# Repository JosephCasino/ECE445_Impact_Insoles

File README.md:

# ECE445_Impact_Insoles
ECE445 Group 68: Impact Insoles - Pressure Sensor System for Running Shoes
Created by: Joseph Casino, Aarush Sivanesan, Matthew Weng

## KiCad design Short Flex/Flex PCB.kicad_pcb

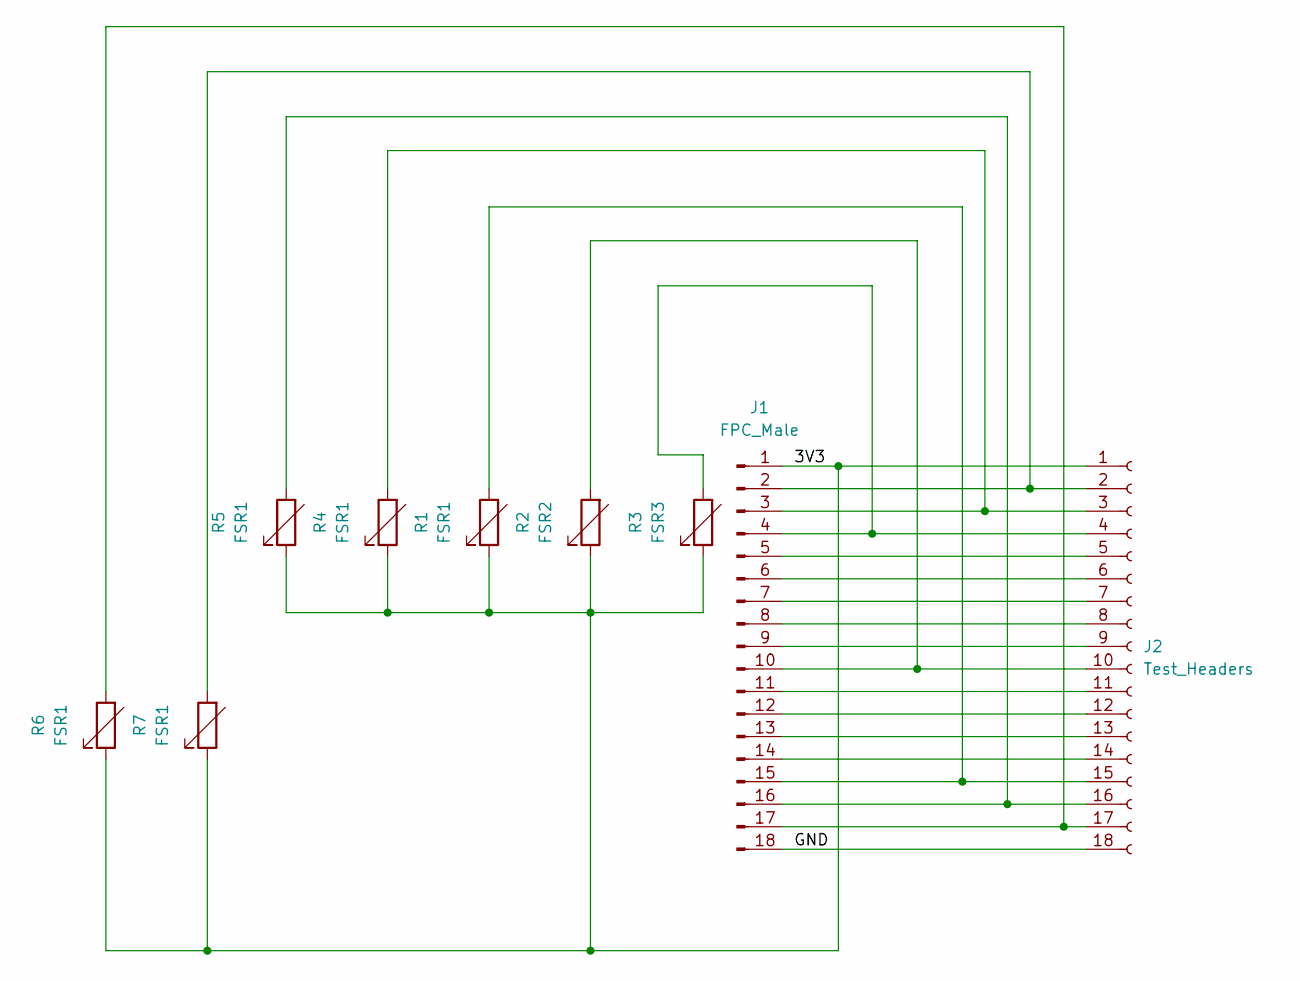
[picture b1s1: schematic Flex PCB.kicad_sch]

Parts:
J1: FPC_Male; FPC-Male-18P-1mm
J2: Test_Headers; PinSocket_1x18_P2.54mm_Vertical
R1, R4, R5, R6, R7: FSR1; FSR_402
R2: FSR2; FSR_402
R3: FSR3; FSR_402

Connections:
/3V3: J1.1, J2.1, R1.1, R2.1, R3.1, R4.1, R5.1, R6.1, R7.1
/GND: J1.18, J2.18
unnamed: J1.2, J2.2, R7.2
unnamed: J1.3, J2.3, R4.2
unnamed: J1.4, J2.4, R3.2
unnamed: J1.5, J2.5
unnamed: J1.6, J2.6
unnamed: J1.7, J2.7
unnamed: J1.8, J2.8
unnamed: J1.9, J2.9
unnamed: J1.10, J2.10, R2.2
unnamed: J1.11, J2.11
unnamed: J1.12, J2.12
unnamed: J1.13, J2.13
unnamed: J1.14, J2.14
unnamed: J1.15, J2.15, R1.2
unnamed: J1.16, J2.16, R5.2
unnamed: J1.17, J2.17, R6.2

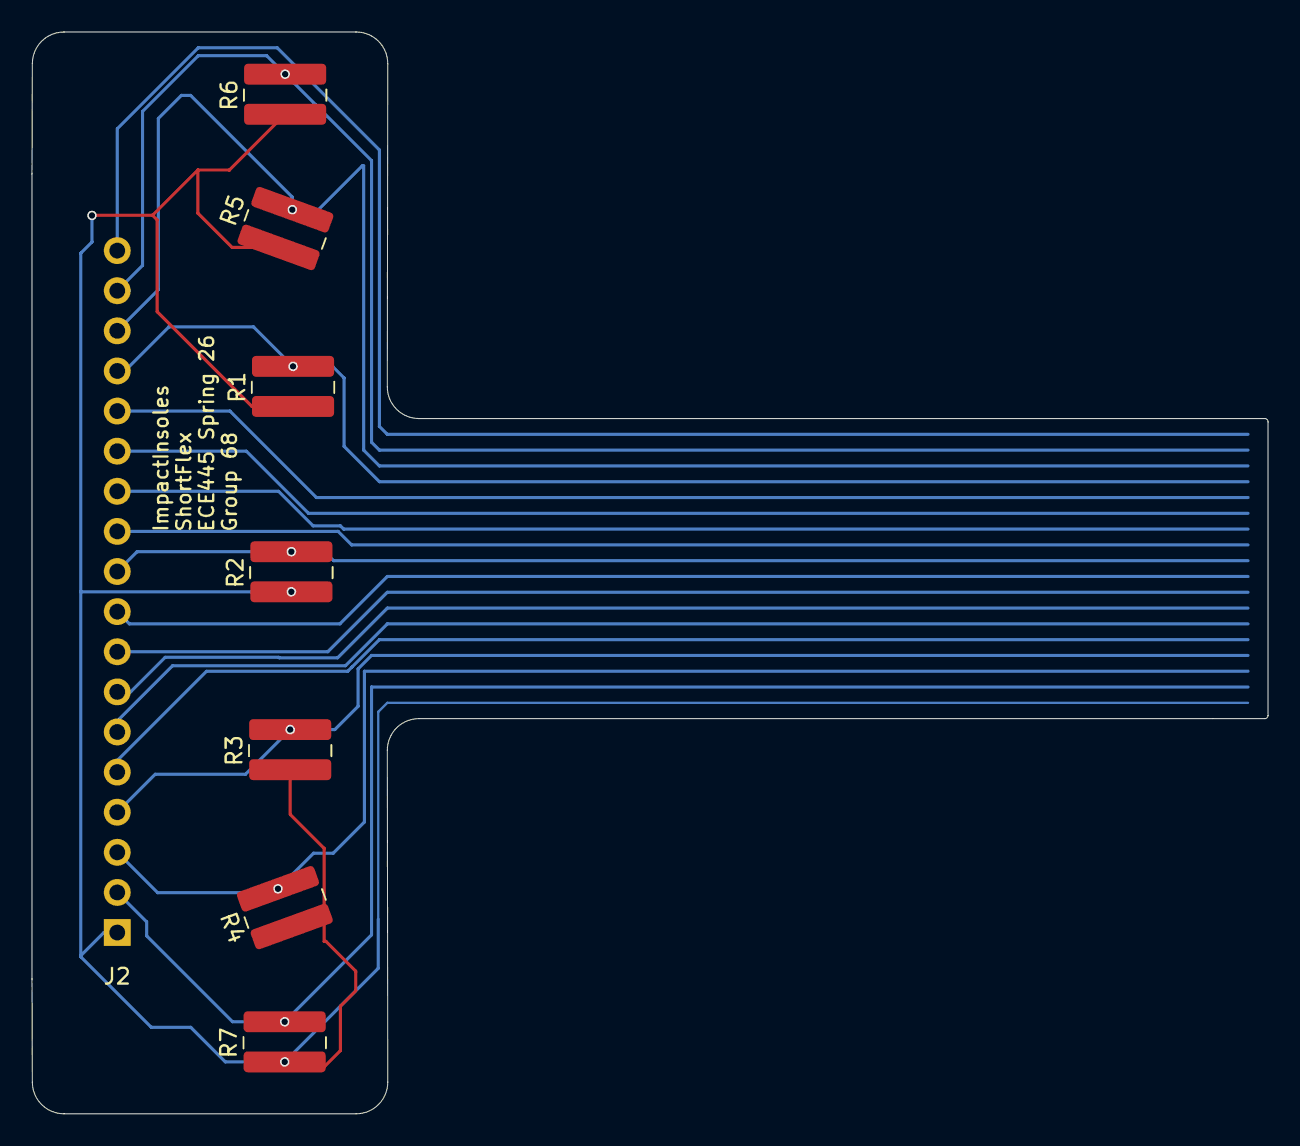
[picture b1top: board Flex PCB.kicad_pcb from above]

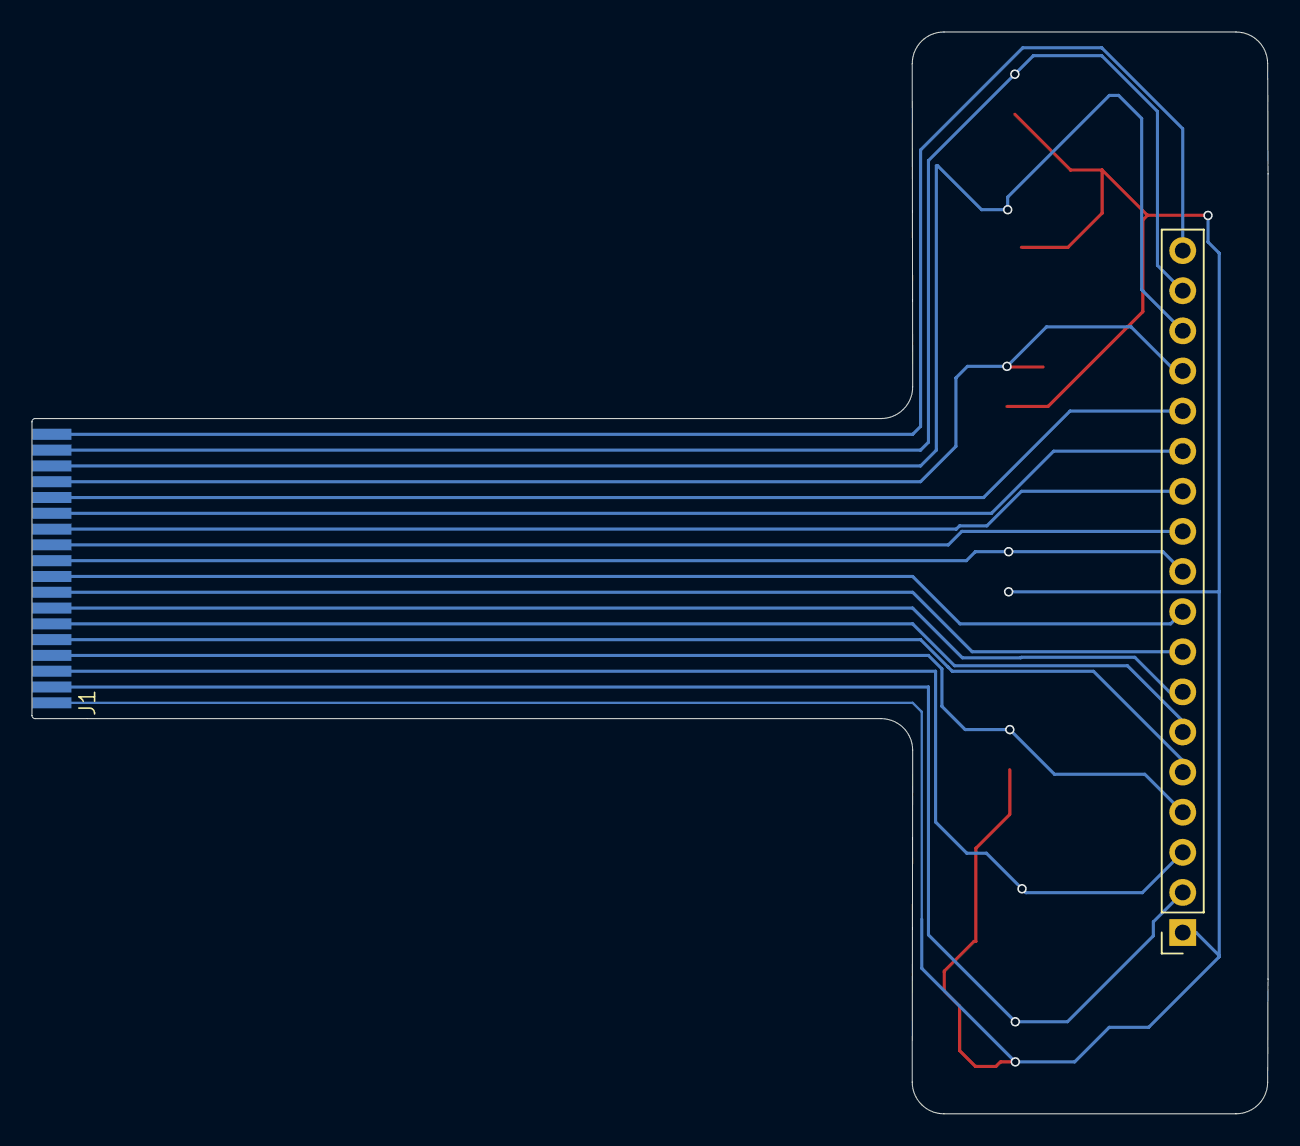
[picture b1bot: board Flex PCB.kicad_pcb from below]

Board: 2 copper layers, 78.3 x 68.5 mm, 9 parts (2 on the bottom side), 18 nets.

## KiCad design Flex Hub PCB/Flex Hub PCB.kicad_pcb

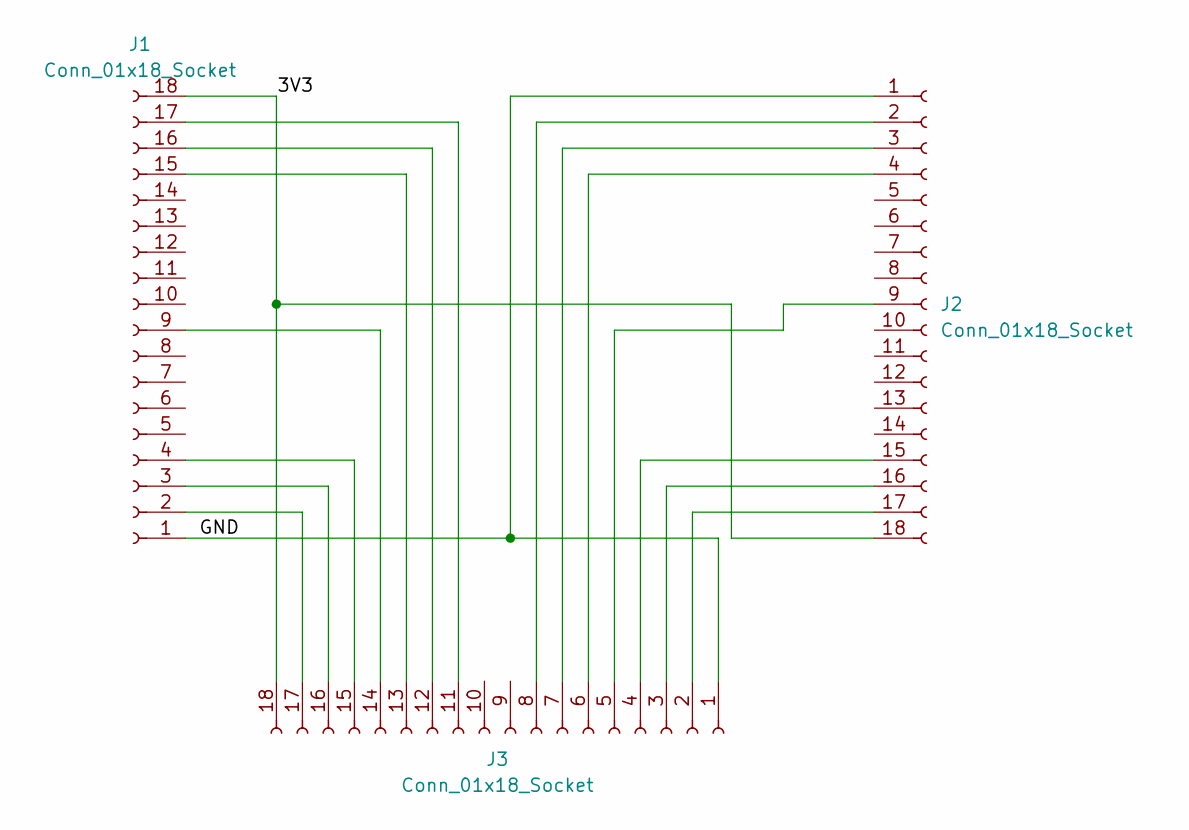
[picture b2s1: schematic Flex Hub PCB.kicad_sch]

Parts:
J1, J2, J3: Conn_01x18_Socket; AMPHENOL_SFW18R-1STE1LF

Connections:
/3V3: J1.18, J2.18, J3.18
/GND: J1.1, J2.1, J3.1
unnamed: J1.2, J3.17
unnamed: J1.3, J3.16
unnamed: J1.4, J3.15
unnamed: J1.9, J3.14
unnamed: J1.15, J3.13
unnamed: J1.16, J3.12
unnamed: J1.17, J3.11
unnamed: J2.2, J3.8
unnamed: J2.3, J3.7
unnamed: J2.4, J3.6
unnamed: J2.9, J3.5
unnamed: J2.15, J3.4
unnamed: J2.16, J3.3
unnamed: J2.17, J3.2

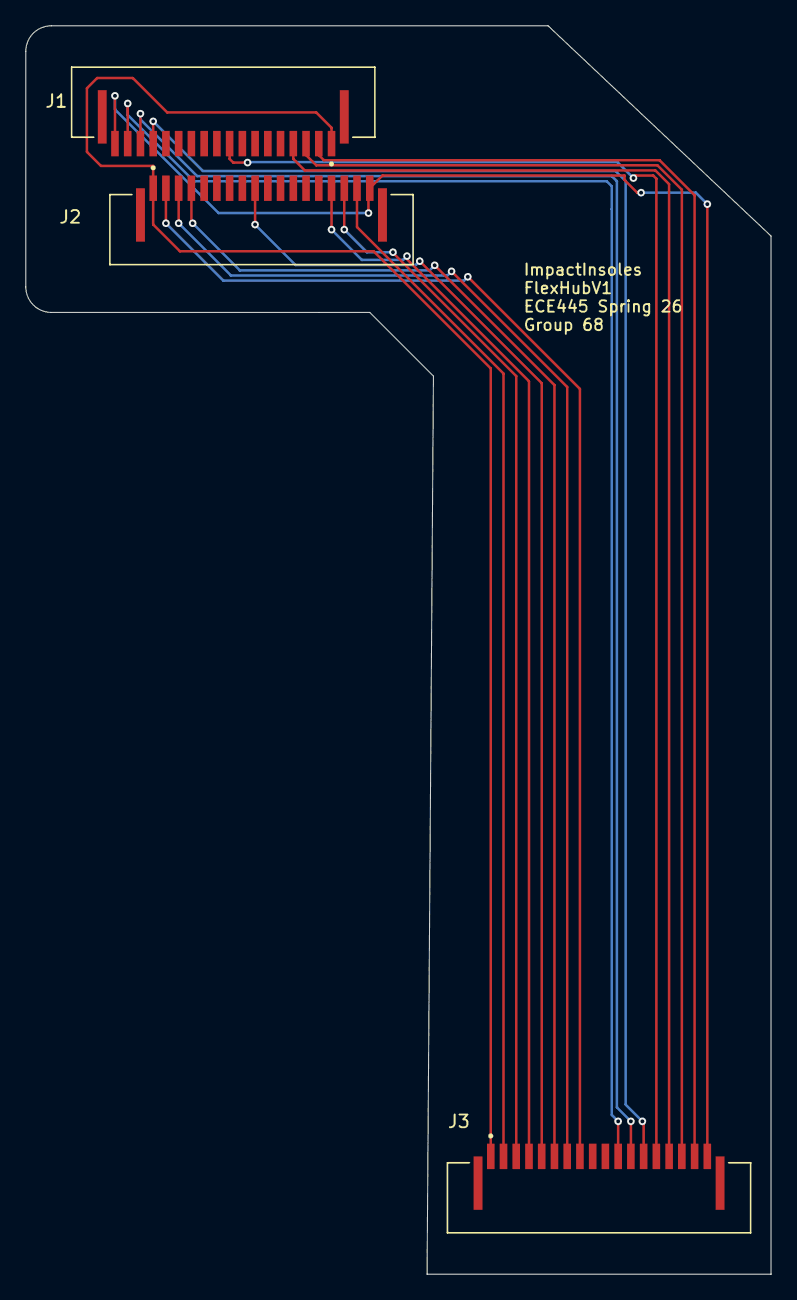
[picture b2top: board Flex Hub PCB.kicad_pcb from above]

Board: 2 copper layers, 58.5 x 98.0 mm, 3 parts (0 on the bottom side), 16 nets.

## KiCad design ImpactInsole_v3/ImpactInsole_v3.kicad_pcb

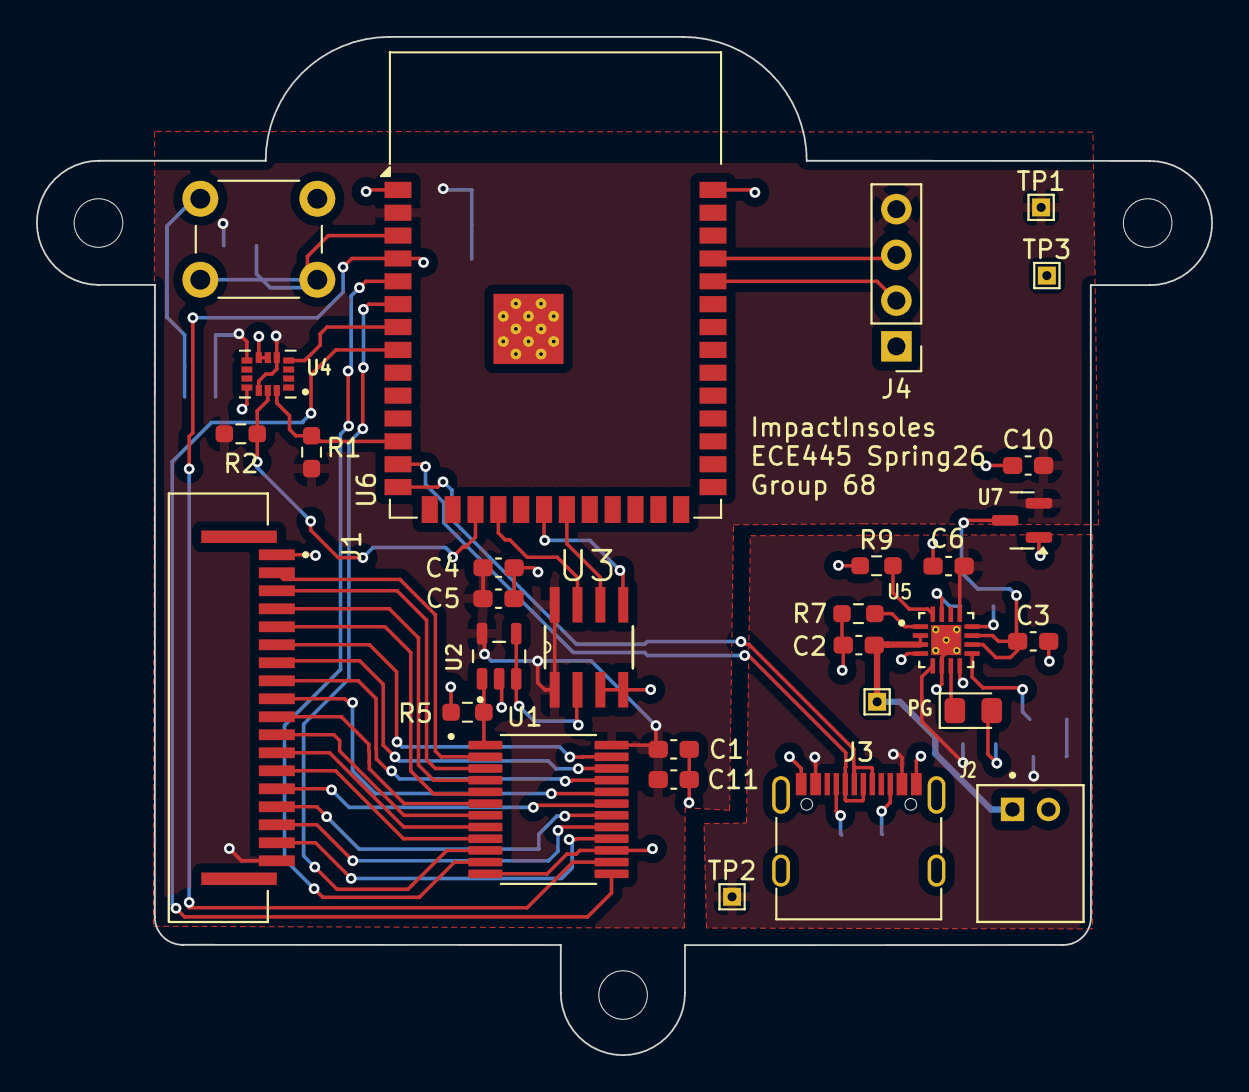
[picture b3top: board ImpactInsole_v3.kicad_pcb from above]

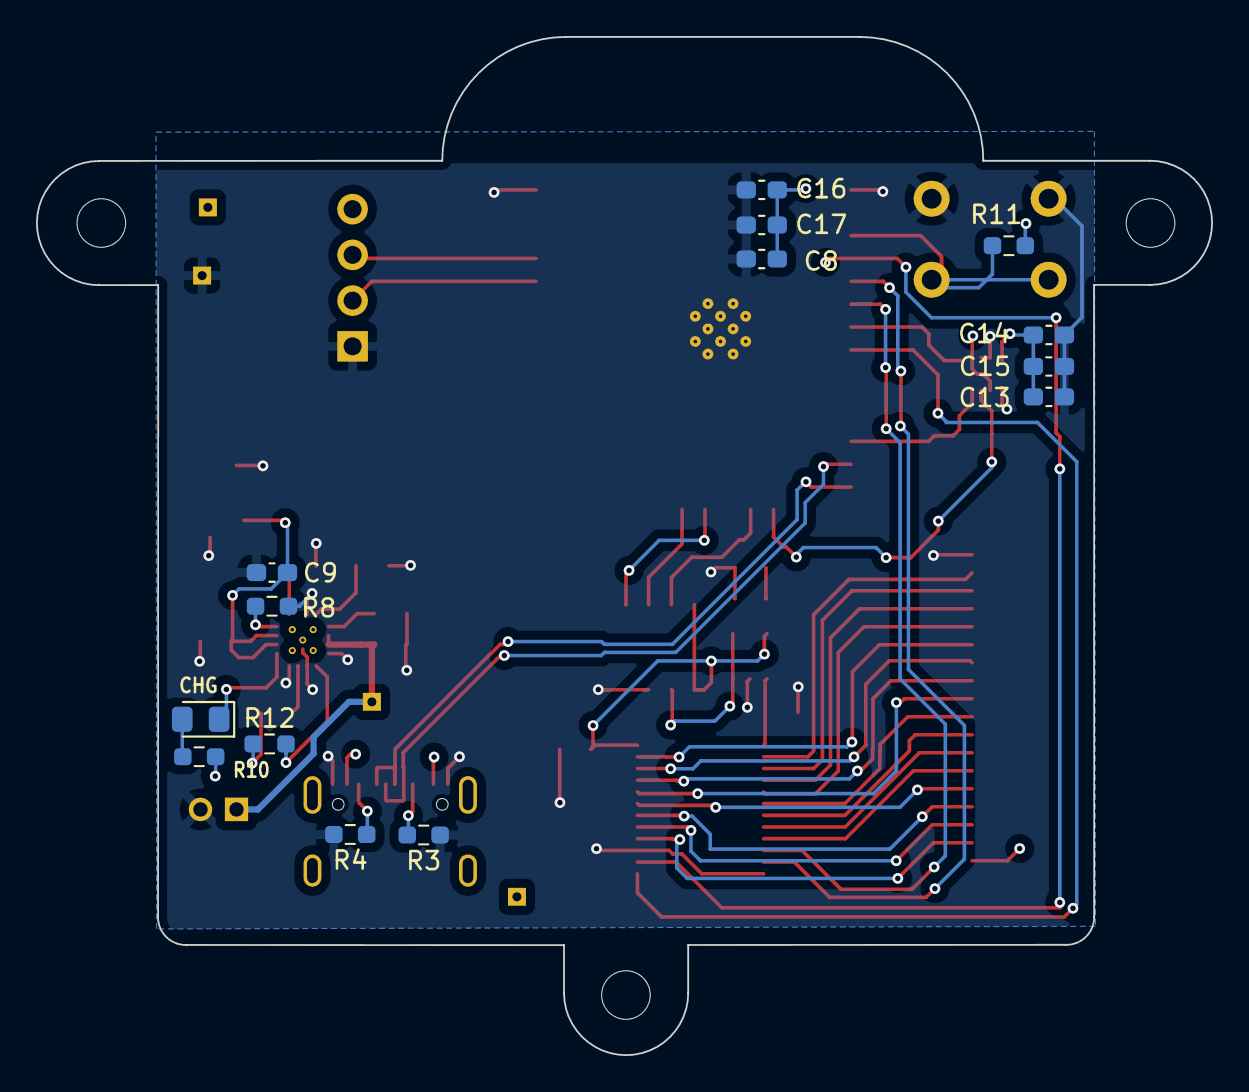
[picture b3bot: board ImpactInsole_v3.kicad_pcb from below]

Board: 2 copper layers, 65.3 x 56.6 mm, 47 parts (14 on the bottom side), 47 nets.

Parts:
C1, C2, C3, C9, C13, C16: 10u; C_0603_1608Metric_Pad1.08x0.95mm_HandSolder
C4, C5, C8, C11, C14: 0.1u; C_0603_1608Metric_Pad1.08x0.95mm_HandSolder
C6: 4.7u; C_0603_1608Metric_Pad1.08x0.95mm_HandSolder
C10, C15, C17: 1u; C_0603_1608Metric_Pad1.08x0.95mm_HandSolder
CHG: LED; LED_0805_2012Metric_Pad1.15x1.40mm_HandSolder
H1, H2, H3: MountingHole; MountingHole_2.7mm_M2.5
J1: SFW18R-1STE1LF; AMPHENOL_SFW18R-1STE1LF
J2: Conn_01x02; JST_S2B-PH-K-S_LF__SN_
J3: USB_C_Receptacle_USB2.0_16P; USB_C_Receptacle_G-Switch_GT-USB-7010ASV
J4: Conn_01x04; PinHeader_1x04_P2.54mm_Vertical
PG: LED; LED_0805_2012Metric_Pad1.15x1.40mm_HandSolder
R1, R2, R5: 4.7k; R_0603_1608Metric_Pad0.98x0.95mm_HandSolder
R3, R4: 5.1k; R_0603_1608Metric_Pad0.98x0.95mm_HandSolder
R7, R11: 10k; R_0603_1608Metric_Pad0.98x0.95mm_HandSolder
R8, R10, R12: 3k; R_0603_1608Metric_Pad0.98x0.95mm_HandSolder
R9: 4.4k; R_0603_1608Metric_Pad0.98x0.95mm_HandSolder
SW1: SW_Push; SW_PUSH_6mm_H5mm
TP1, TP2, TP3, TP5: TestPoint; TestPoint_THTPad_1.0x1.0mm_Drill0.5mm
U1: CD74HC4067SM96; SOP65P780X200-24N
U2: TLV9001IDBVR; SOT95P280X145-5N
U3: MCP3201T-CI_SN; SOIC127P600X175-8N
U4: LSM6DSOXTR; PQFN50P250X300X86-14N
U5: BQ24075RGTR; QFN50P300X300X100-17N
U6: ESP32-S3-WROOM-1
U7: MCP1700x-300xxTT; SOT-23

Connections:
+3V3: C1.1, C4.1, C5.1, C8.1, C10.1, C11.1, C13.1, C14.1, C15.1, C16.1, C17.1, J1.18, J4.4, R1.1, R2.1, R11.1, TP1.1, U1.24 (VCC), U2.5 (V+), U3.1 (VREF), U3.8 (VDD), U4.5 (VDDIO), U4.8 (VDD), U4.12 (CS), U6.2 (3V3), U7.2 (VO)
/MCU/ADC_CLK: U3.5 (~CS/SHDN), U6.20 (IO12)
/MCU/ADC_CS: U3.7 (CLK), U6.18 (IO10)
/MCU/ADC_SDATA: U3.6 (DOUT), U6.21 (IO13)
/MCU/IMU_Clk: R2.2, U4.13 (SCL), U6.17 (IO9)
/MCU/IMU_Data: R1.2, U4.14 (SDA), U6.12 (IO8)
/MCU/IMU_INT: U4.4 (INT1), U6.7 (IO7)
/MCU/Rx_D: J4.2, U6.36 (RXD0)
/MCU/S0: U1.14 (S2), U6.4 (IO4)
/MCU/S1: U1.11 (S1), U6.5 (IO5)
/MCU/S2: U1.10 (S0), U6.6 (IO6)
/MCU/S3: U1.13 (S3), U6.8 (IO15)
/MCU/Tx_D: J4.3, U6.37 (TXD0)
/MCU/USB_D_N: J3.A7 (D-), J3.B7 (D-), U6.13 (USB_D-)
/MCU/USB_D_P: J3.A6 (D+), J3.B6 (D+), U6.14 (USB_D+)
/MCU/VDD5V: C6.1, J3.A4 (VBUS), J3.A9 (VBUS), J3.B4 (VBUS), J3.B9 (VBUS), R10.1, R12.2, TP2.1, U5.5 (EN2), U5.13 (IN)
/Sensor/Mux_Out: R5.1, U1.1 (COMMON_I/O), U2.1 (IN+)
/Sensor/sense1: J1.17, U1.16 (I15)
/Sensor/sense2: J1.16, U1.17 (I14)
/Sensor/sense3: J1.15, U1.18 (I13)
/Sensor/sense4: J1.14, U1.19 (I12)
/Sensor/sense5: J1.13, U1.9 (I0)
/Sensor/sense6: J1.12, U1.8 (I1)
/Sensor/sense7: J1.11, U1.7 (I2)
/Sensor/sense8: J1.10, U1.6 (I3)
/Sensor/sense9: J1.9, U1.20 (I11)
/Sensor/sense10: J1.8, U1.21 (I10)
/Sensor/sense11: J1.7, U1.22 (I9)
/Sensor/sense12: J1.6, U1.23 (I8)
/Sensor/sense13: J1.5, U1.5 (I4)
/Sensor/sense14: J1.4, U1.4 (I5)
/Sensor/sense15: J1.3, U1.3 (I6)
/Sensor/sense16: J1.2, U1.2 (I7)
GND: C1.2, C2.2, C3.2, C4.2, C5.2, C6.2, C8.2, C9.2, C10.2, C11.2, C13.2, C14.2, C15.2, C16.2, C17.2, J1.1, J2.2, J3.A1 (GND), J3.A12 (GND), J3.B1 (GND), J3.B12 (GND), J4.1, R3.1, R4.2, R5.2, R7.1, R8.1, R9.1, SW1.1, TP3.1, U1.12 (GND), U1.15 (~E), U2.2 (V-), U3.3 (IN-), U3.4 (VSS), U4.6 (GND), U4.7 (GND), U4.11 (SDO_AUX), U5.4 (~CE), U5.6 (EN1), U5.8 (VSS), U5.15 (SYSOFF), U5.17 (EXP), U6.1 (GND), U6.40 (GND), U6.41 (GND), U7.1 (GND)
unnamed: CHG.2 (A), R10.2
unnamed: CHG.1 (K), U5.9 (~CHG)
unnamed: PG.2 (A), R12.1
unnamed: PG.1 (K), U5.7 (~PGOOD)
unnamed: C2.1, J2.1, TP5.1, U5.2 (BAT_2), U5.3 (BAT_3)
unnamed: J3.A5 (CC1), R3.2
unnamed: J3.B5 (CC2), R4.1
unnamed: U2.3 (IN-), U2.4 (OUT), U3.2 (IN+)
unnamed: R8.2, U5.12 (ILIM)
unnamed: R9.2, U5.16 (ISET)
unnamed: C3.1, C9.1, U5.10 (OUT_10), U5.11 (OUT_11), U7.3 (VI)
unnamed: R7.2, U5.1 (TS)
unnamed: R11.2, SW1.2, U6.3 (EN)

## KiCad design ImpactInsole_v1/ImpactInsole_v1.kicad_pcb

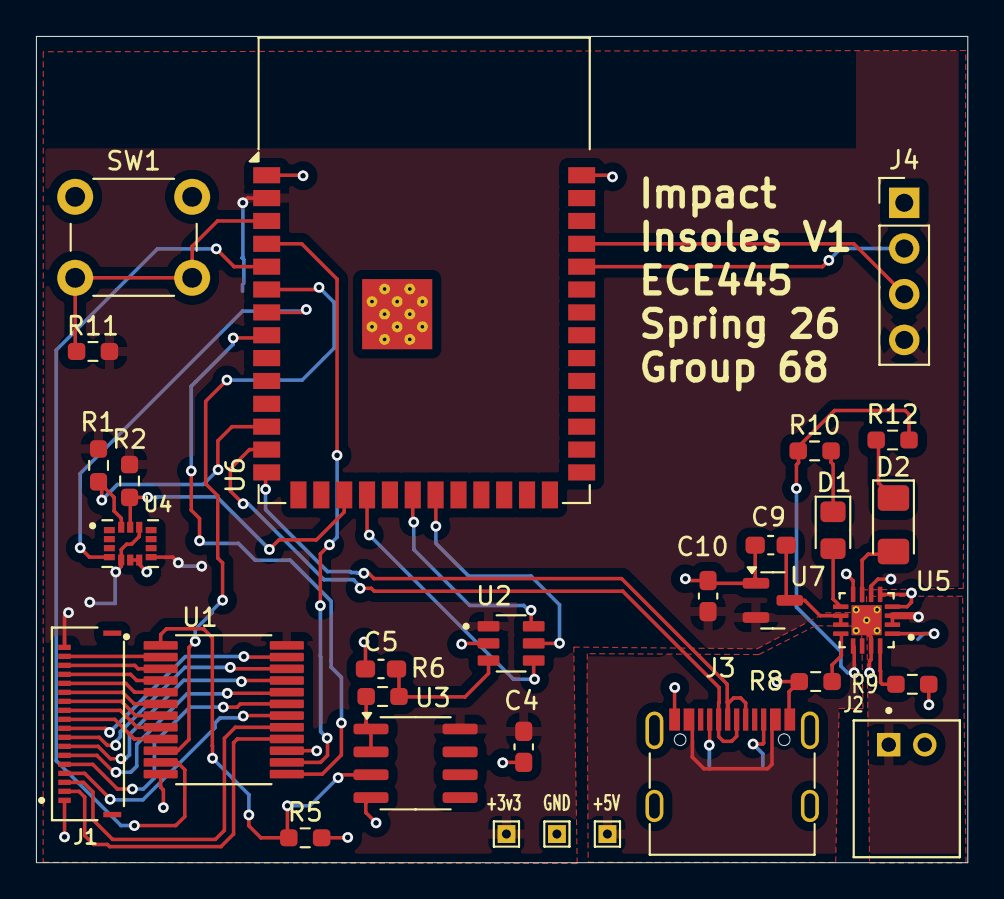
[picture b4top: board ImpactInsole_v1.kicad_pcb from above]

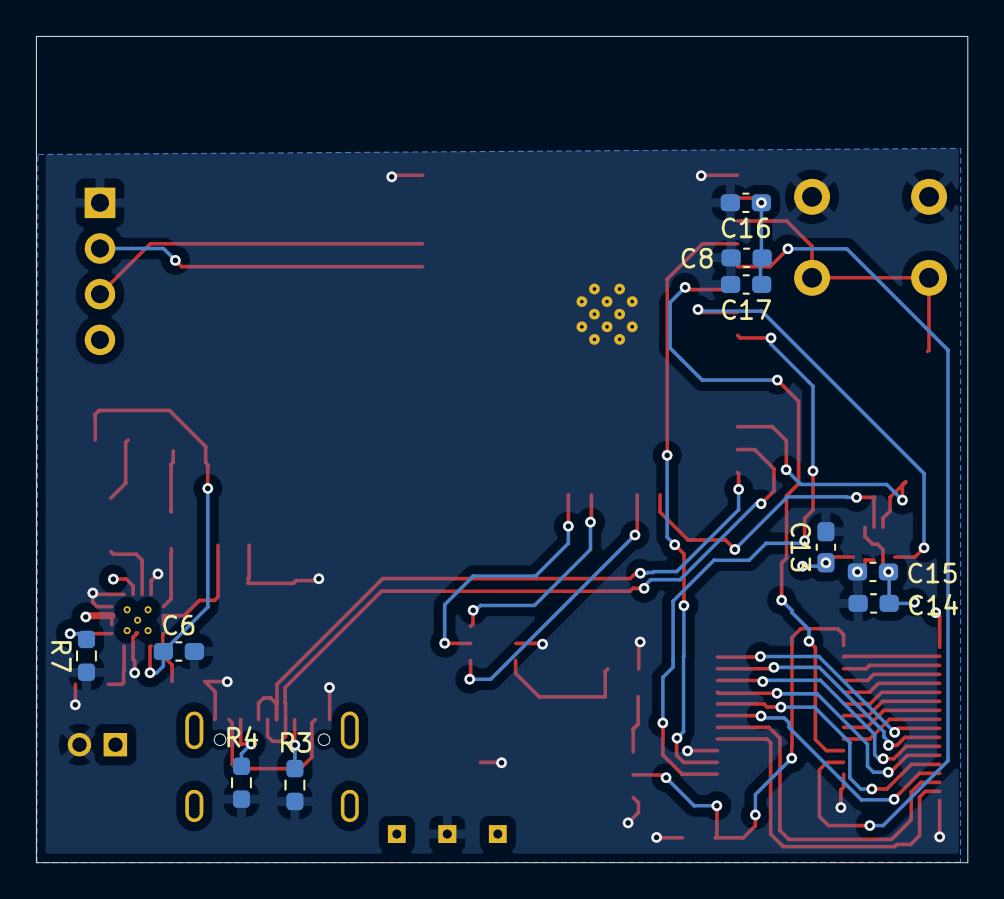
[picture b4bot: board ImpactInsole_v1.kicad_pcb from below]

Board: 2 copper layers, 51.7 x 45.9 mm, 40 parts (10 on the bottom side), 48 nets.

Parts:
+3v3, +5V: TestPoint; TestPoint_THTPad_1.0x1.0mm_Drill0.5mm
C4, C8, C14: 0.1u; C_0603_1608Metric_Pad1.08x0.95mm_HandSolder
C5, C10, C15, C17: 1u; C_0603_1608Metric_Pad1.08x0.95mm_HandSolder
C6: 4.7u; C_0603_1608Metric_Pad1.08x0.95mm_HandSolder
C9, C13, C16: 10u; C_0603_1608Metric_Pad1.08x0.95mm_HandSolder
D1: LED; LED_0805_2012Metric_Pad1.15x1.40mm_HandSolder
D2: LED; LED_1206_3216Metric_Pad1.42x1.75mm_HandSolder
GND: TestPoint; TestPoint_THTPad_1.0x1.0mm_Drill0.5mm
J1: 503480-1800; MOLEX_503480-1800
J2: Conn_01x02; JST_S2B-PH-K-S_LF__SN_
J3: USB_C_Receptacle_USB2.0_16P; USB_C_Receptacle_G-Switch_GT-USB-7010ASV
J4: Conn_01x04; PinHeader_1x04_P2.54mm_Vertical
R1, R2, R6: 4.7k; R_0603_1608Metric_Pad0.98x0.95mm_HandSolder
R3, R4: 5.1k; R_0603_1608Metric_Pad0.98x0.95mm_HandSolder
R5: 30k; R_0603_1608Metric_Pad0.98x0.95mm_HandSolder
R7, R11: 10k; R_0603_1608Metric_Pad0.98x0.95mm_HandSolder
R8, R10, R12: 3k; R_0603_1608Metric_Pad0.98x0.95mm_HandSolder
R9: 4.4k; R_0603_1608Metric_Pad0.98x0.95mm_HandSolder
SW1: SW_Push; SW_PUSH_6mm_H5mm
U1: CD74HC4067SM96; SOP65P780X200-24N
U2: ADC081S021CIMF; SOT95P280X145-6N
U3: OPA1662D; SOIC-8_3.9x4.9mm_P1.27mm
U4: LSM6DSOXTR; PQFN50P250X300X86-14N
U5: BQ24075RGTR; QFN50P300X300X100-17N
U6: ESP32-S3-WROOM-1
U7: MCP1700x-300xxTT; SOT-23

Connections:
+3V3: +3v3.1, C4.1, C8.1, C10.1, C13.1, C14.1, C15.1, C16.1, C17.1, J1.18, J4.4, R1.1, R2.1, R11.1, U1.24 (VCC), U2.1 (VA), U3.8 (V+), U4.5 (VDDIO), U4.8 (VDD), U4.12 (CS), U5.6 (EN1), U6.2 (3V3), U7.2 (VO)
/MCU/ADC_CLK: U2.6 (~CS), U6.20 (IO12)
/MCU/ADC_CS: U2.4 (SCLK), U6.18 (IO10)
/MCU/ADC_SDATA: U2.5 (SDATA), U6.21 (IO13)
/MCU/IMU_Clk: R2.2, U4.13 (SCL), U6.17 (IO9)
/MCU/IMU_Data: R1.2, U4.14 (SDA), U6.12 (IO8)
/MCU/IMU_INT: U4.4 (INT1), U6.7 (IO7)
/MCU/Rx_D: J4.2, U6.36 (RXD0)
/MCU/S0: U1.14 (S2), U6.4 (IO4)
/MCU/S1: U1.11 (S1), U6.5 (IO5)
/MCU/S2: U1.10 (S0), U6.6 (IO6)
/MCU/S3: U1.13 (S3), U6.8 (IO15)
/MCU/Tx_D: J4.3, U6.37 (TXD0)
/MCU/USB_D_N: J3.A7 (D-), J3.B7 (D-), U6.13 (USB_D-)
/MCU/USB_D_P: J3.A6 (D+), J3.B6 (D+), U6.14 (USB_D+)
/MCU/VDD5V: +5V.1, C6.1, J3.A4 (VBUS), J3.A9 (VBUS), J3.B4 (VBUS), J3.B9 (VBUS), R10.1, R12.2, U5.13 (IN)
/Sensor/Mux_Out: R5.1, U1.1 (COMMON_I/O), U3.3 (+)
/Sensor/sense1: J1.17, U1.2 (I7)
/Sensor/sense2: J1.16, U1.3 (I6)
/Sensor/sense3: J1.15, U1.4 (I5)
/Sensor/sense4: J1.14, U1.5 (I4)
/Sensor/sense5: J1.13, U1.6 (I3)
/Sensor/sense6: J1.12, U1.7 (I2)
/Sensor/sense7: J1.11, U1.8 (I1)
/Sensor/sense8: J1.10, U1.9 (I0)
/Sensor/sense9: J1.9, U1.23 (I8)
/Sensor/sense10: J1.8, U1.22 (I9)
/Sensor/sense11: J1.7, U1.21 (I10)
/Sensor/sense12: J1.6, U1.20 (I11)
/Sensor/sense13: J1.5, U1.19 (I12)
/Sensor/sense14: J1.4, U1.18 (I13)
/Sensor/sense15: J1.3, U1.17 (I14)
/Sensor/sense16: J1.2, U1.16 (I15)
GND: C4.2, C5.2, C6.2, C8.2, C9.2, C10.2, C13.2, C14.2, C15.2, C16.2, C17.2, GND.1, J1.1, J2.2, J3.A1 (GND), J3.A12 (GND), J3.B1 (GND), J3.B12 (GND), J4.1, R3.1, R4.2, R5.2, R7.1, R8.1, R9.1, SW1.1, U1.12 (GND), U1.15 (~E), U2.2 (GND), U3.4 (V-), U4.6 (GND), U4.7 (GND), U5.4 (~CE), U5.5 (EN2), U5.8 (VSS), U5.15 (SYSOFF), U5.17 (EXP), U6.1 (GND), U6.40 (GND), U6.41 (GND), U7.1 (GND)
unnamed: D1.2 (A), U5.9 (~CHG)
unnamed: D1.1 (K), R10.2
unnamed: D2.2 (A), U5.7 (~PGOOD)
unnamed: D2.1 (K), R12.1
unnamed: J2.1, U5.2 (BAT_2), U5.3 (BAT_3)
unnamed: J3.A5 (CC1), R3.2
unnamed: J3.B5 (CC2), R4.1
unnamed: C5.1, R6.2, U2.3 (VIN)
unnamed: R6.1, U3.1, U3.2 (-)
unnamed: R8.2, U5.12 (ILIM)
unnamed: R9.2, U5.16 (ISET)
unnamed: C9.1, U5.10 (OUT_10), U5.11 (OUT_11), U7.3 (VI)
unnamed: R7.2, U5.1 (TS)
unnamed: R11.2, SW1.2, U6.3 (EN)

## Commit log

2026-02-17 notebook create
2026-02-17 notebook file create (...)
2026-02-17 J- created dummy app
2026-02-17 aarush notebook update
2026-02-17 Create README.md for Matthew's Lab
    Added initial content for Matthew's lab notebook, including details about a BOM work session and relevant links.
2026-02-20 pcb proto
2026-02-20 aarush 2/19 notebook update
2026-02-21 pcb begnnings + more libs
2026-02-21 notebook matthew entries
2026-02-21 Revise README with latest PCB design updates
    Updated the README to reflect recent work on the PCB schematic, battery selection, and design considerations. Added images of the current schematic and rough layout.
2026-02-21 Update README with lab notebook entries
2026-02-24 updated git + notebook
2026-02-24 updated Joseph's notebook in main branch
2026-02-26 Flex PCB v1
2026-02-26 File cleanup
2026-02-26 idk pcb n shi
2026-02-26 updated notebook
2026-02-26 aarush check + gerber gen
2026-02-26 updated silkscreen thickness + gerbers
2026-02-26 fixed silkscreen warnings
2026-03-09 "trying web hosting for ioS bluetooth workaround"
2026-03-09 Simple app made - testing xCode
2026-03-09 manifest trial
2026-03-09 added manifest.json
2026-03-09 moved manifest.json
2026-03-09 manifest with icons
2026-03-09 changed UI
2026-03-10 packet loss test + 12 bit resolution
2026-03-10 updated packet loss test, reconnect bluetooth fix?
2026-03-10 updated for 4 potentiometers
2026-03-12 updated silkscreens - sent for round 3
2026-03-12 Flex PCB v2
2026-03-23 group roadmap
2026-03-23 Added Software Side
2026-03-24 pushed notebook to be up to date
2026-03-24 Revise README with lab notebook entries and updates
    Updated the README with detailed notes on lab sessions, decisions made regarding battery types, schematic progress, and design iterations for the PCB.
2026-03-24 Revise README.md with lab notebook updates
    Updated the README.md to include additional entries and details about the lab notebook sessions, including decisions on battery types, schematic updates, and design progress.
2026-03-25 added to roadmap
2026-03-26 v3 and stuff
2026-03-26 Flex Hub PCB
2026-03-26 Shortened Flex v2
2026-03-26 Final flex designs and gerbers
2026-04-02 After all r4 edits (late)
2026-04-06 fully update website!
2026-04-06 updated footmap
2026-04-06 demo mode for changing UI
2026-04-07 added force value column
2026-04-07 adjusted foot heatmap
2026-04-07 fixed session graph bug
2026-04-19 EnclosureV1STLs
2026-04-21 new and improved web app
2026-04-21 visual improvements, UI changes
2026-04-21 collapsable sessions, UI changes
2026-04-21 gait event freeze, IMU placeholders!
2026-04-24 reconfigured sensor placement
2026-04-24 reconfigured sensor labels
2026-04-24 reconfigured sensor placement again
2026-04-26 More enclosure
2026-04-26 reconfigured foot heat map
2026-04-26 deleted IMU from web app
2026-04-26 adjusted 400 vs 402 sensors
2026-04-26 changed FSR400 scale
2026-04-28 SCUFF TEST - sensor step calibration
2026-04-28 REVERT
2026-04-28 added raw ADC value recording to csv option
2026-04-28 added Force to CSV recording session
2026-04-28 new step count logic - gait phases added
2026-04-28 adjusted step logic
2026-04-28 removed AI analysis and split up foot zones
2026-04-29 moved heat map circles, changed color dynamics
2026-04-29 revert color dynamics, changed foot shape
2026-04-29 changed foot shape
2026-04-29 added verification tab
2026-04-29 fixed gait events?
2026-04-29 updated manifest.json
2026-04-29 added live sample rate
2026-04-29 changed session graph to a cadence over time
2026-04-29 updated sample rate
2026-05-06 Revise README.md with latest lab notebook entries
    Updated the README.md to include additional entries and details about the lab notebook activities, including design sessions, component decisions, and PCB layouts.
2026-05-07 Update matthew notebook in main
2026-05-07 Aarush's Notebook
2026-05-07 Joseph's notebook finally pushed
2026-05-07 Added Final PCB Arduino Firmware Code
2026-05-07 Merged with newer version from Drive that has some equations and things
